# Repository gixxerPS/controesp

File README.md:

# controesp
controllino like board for esp

## PCB size

- base
86.5 x 84 mm
- hat
57 x 80 mm

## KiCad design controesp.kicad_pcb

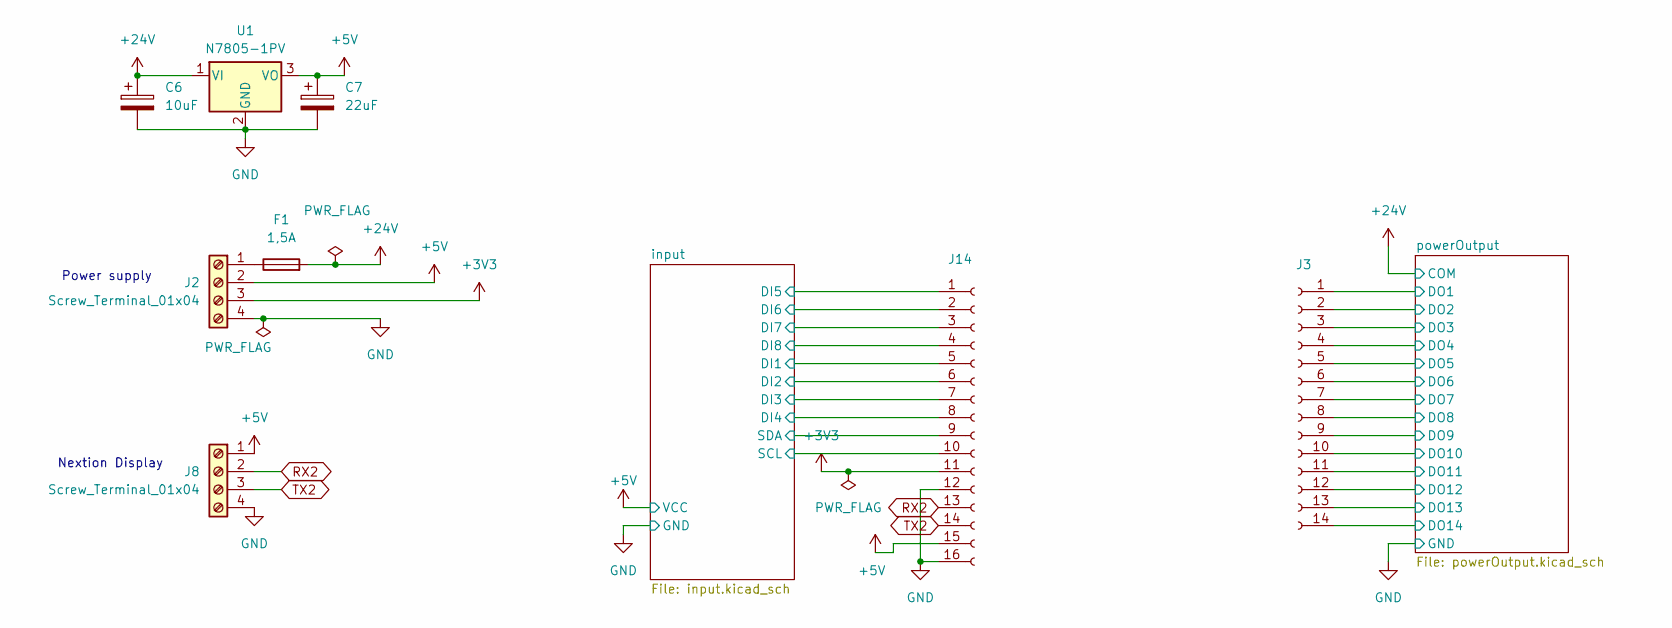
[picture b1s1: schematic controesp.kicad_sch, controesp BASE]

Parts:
C6: 10uF; CP_EIA-3216-12_Kemet-S_Pad1.58x1.35mm_HandSolder; LCSC C13585
C7: 22uF; CP_EIA-2012-12_Kemet-R_Pad1.30x1.05mm_HandSolder; LCSC C45783
F1: 1,5A; Fuseholder_Littelfuse_Nano2_154x
J2, J8: Screw_Terminal_01x04; PhoenixContact_MC_1,5_4-G-3.5_1x04_P3.50mm_Horizontal; LCSC C5241865
J3: Conn_01x14_Socket; PinSocket_1x14_P2.54mm_Vertical; LCSC C52711
J14: Conn_01x16_Socket; PinSocket_1x16_P2.54mm_Vertical; LCSC C66987
U1: N7805-1PV; TO-220-3_Vertical

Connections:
+3V3: J2.3, J14.11
+5V: C7.1, J2.2, J8.1, J14.15, U1.3 (VO); also elsewhere on the board
+24V: C6.1, F1.2, U1.1 (VI); also elsewhere on the board
/input/DI1: J14.5; also elsewhere on the board
/input/DI2: J14.6; also elsewhere on the board
/input/DI3: J14.7; also elsewhere on the board
/input/DI4: J14.8; also elsewhere on the board
/input/DI5: J14.1; also elsewhere on the board
/input/DI6: J14.2; also elsewhere on the board
/input/DI7: J14.3; also elsewhere on the board
/input/DI8: J14.4; also elsewhere on the board
/input/SCL: J14.10; also elsewhere on the board
/input/SDA: J14.9; also elsewhere on the board
/powerOutput/DO1: J3.1; also elsewhere on the board
/powerOutput/DO2: J3.2; also elsewhere on the board
/powerOutput/DO3: J3.3; also elsewhere on the board
/powerOutput/DO4: J3.4; also elsewhere on the board
/powerOutput/DO5: J3.5; also elsewhere on the board
/powerOutput/DO6: J3.6; also elsewhere on the board
/powerOutput/DO7: J3.7; also elsewhere on the board
/powerOutput/DO8: J3.8; also elsewhere on the board
/powerOutput/DO9: J3.9; also elsewhere on the board
/powerOutput/DO10: J3.10; also elsewhere on the board
/powerOutput/DO11: J3.11; also elsewhere on the board
/powerOutput/DO12: J3.12; also elsewhere on the board
/powerOutput/DO13: J3.13; also elsewhere on the board
/powerOutput/DO14: J3.14; also elsewhere on the board
GND: C6.2, C7.2, J2.4, J8.4, J14.12, J14.16, U1.2 (GND); also elsewhere on the board
unnamed: F1.1, J2.1
RX2: J8.2, J14.13
TX2: J8.3, J14.14

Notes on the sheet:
Power supply
Nextion Display

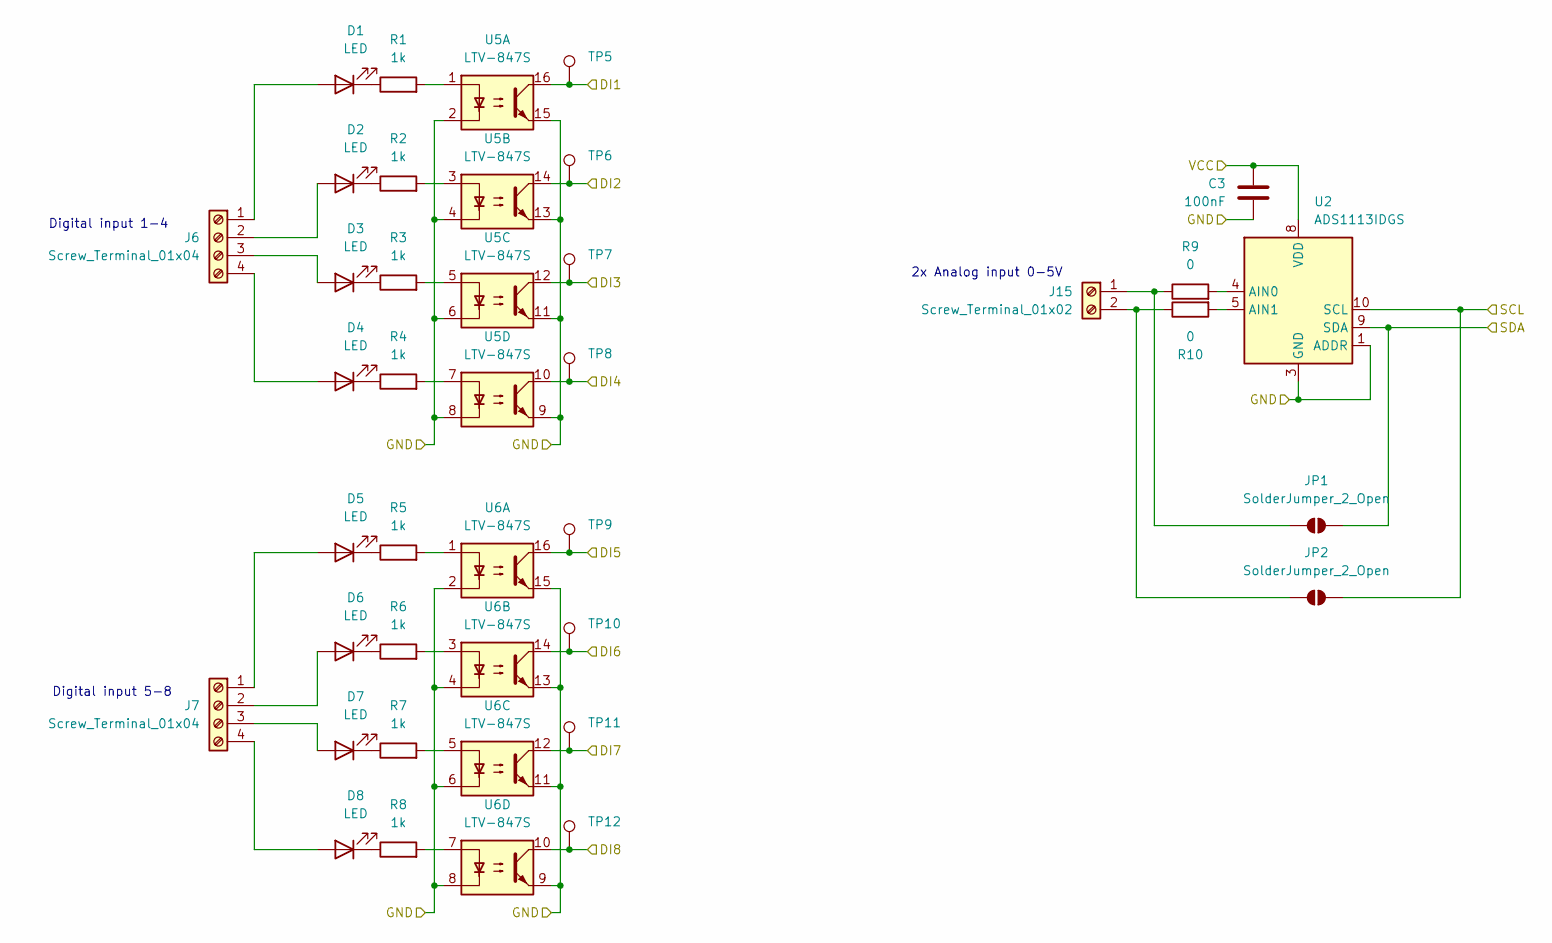
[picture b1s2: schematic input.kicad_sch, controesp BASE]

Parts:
C3: 100nF; C_0805_2012Metric_Pad1.18x1.45mm_HandSolder; LCSC C49678
D1, D2, D3, D4, D5, D6, D7, D8: LED; LED_0805_2012Metric_Pad1.15x1.40mm_HandSolder; LCSC C2297
J6, J7: Screw_Terminal_01x04; PhoenixContact_MC_1,5_4-G-3.5_1x04_P3.50mm_Horizontal; LCSC C5241865
J15: Screw_Terminal_01x02; PhoenixContact_MC_1,5_2-G-3.5_1x02_P3.50mm_Horizontal; LCSC C61791
JP1, JP2: SolderJumper_2_Open; SolderJumper-2_P1.3mm_Open_Pad1.0x1.5mm
R1, R2, R3, R4, R5, R6, R7, R8: 1k; R_0805_2012Metric_Pad1.20x1.40mm_HandSolder; LCSC C17513
R9, R10: 0; R_0805_2012Metric_Pad1.20x1.40mm_HandSolder; LCSC C17477
TP5, TP6, TP7, TP8, TP9, TP10, TP11, TP12: TestPoint_Pad_D1.5mm
U2: ADS1113IDGS; TSSOP-10_3x3mm_P0.5mm; LCSC C2651336
U5: LTV-847S; SMDIP-16_W9.53mm; LCSC C114599
U6: LTV-847S; SMDIP-16_W9.53mm

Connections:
+5V: C3.1, U2.8 (VDD); also elsewhere on the board
/input/DI1: TP5.1, U5.16; also elsewhere on the board
/input/DI2: TP6.1, U5.14; also elsewhere on the board
/input/DI3: TP7.1, U5.12; also elsewhere on the board
/input/DI4: TP8.1, U5.10; also elsewhere on the board
/input/DI5: TP9.1, U6.16; also elsewhere on the board
/input/DI6: TP10.1, U6.14; also elsewhere on the board
/input/DI7: TP11.1, U6.12; also elsewhere on the board
/input/DI8: TP12.1, U6.10; also elsewhere on the board
/input/SCL: JP2.2 (B), U2.10 (SCL); also elsewhere on the board
/input/SDA: JP1.2 (B), U2.9 (SDA); also elsewhere on the board
GND: C3.2, U2.1 (ADDR), U2.3 (GND), U5.2, U5.4, U5.6, U5.8, U5.9, U5.11, U5.13, U5.15, U6.2, U6.4, U6.6, U6.8, U6.9, U6.11, U6.13, U6.15; also elsewhere on the board
unnamed: D1.2 (A), J6.1
unnamed: D1.1 (K), R1.1
unnamed: D2.2 (A), J6.2
unnamed: D2.1 (K), R2.1
unnamed: D3.2 (A), J6.3
unnamed: D3.1 (K), R3.1
unnamed: D4.2 (A), J6.4
unnamed: D4.1 (K), R4.1
unnamed: D5.2 (A), J7.1
unnamed: D5.1 (K), R5.1
unnamed: D6.2 (A), J7.2
unnamed: D6.1 (K), R6.1
unnamed: D7.2 (A), J7.3
unnamed: D7.1 (K), R7.1
unnamed: D8.2 (A), J7.4
unnamed: D8.1 (K), R8.1
unnamed: J15.1, JP1.1 (A), R9.1
unnamed: J15.2, JP2.1 (A), R10.1
unnamed: R1.2, U5.1
unnamed: R2.2, U5.3
unnamed: R3.2, U5.5
unnamed: R4.2, U5.7
unnamed: R5.2, U6.1
unnamed: R6.2, U6.3
unnamed: R7.2, U6.5
unnamed: R8.2, U6.7
unnamed: R9.2, U2.4 (AIN0)
unnamed: R10.2, U2.5 (AIN1)

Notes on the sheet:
2x Analog input 0-5V
Digital input 5-8
Digital input 1-4

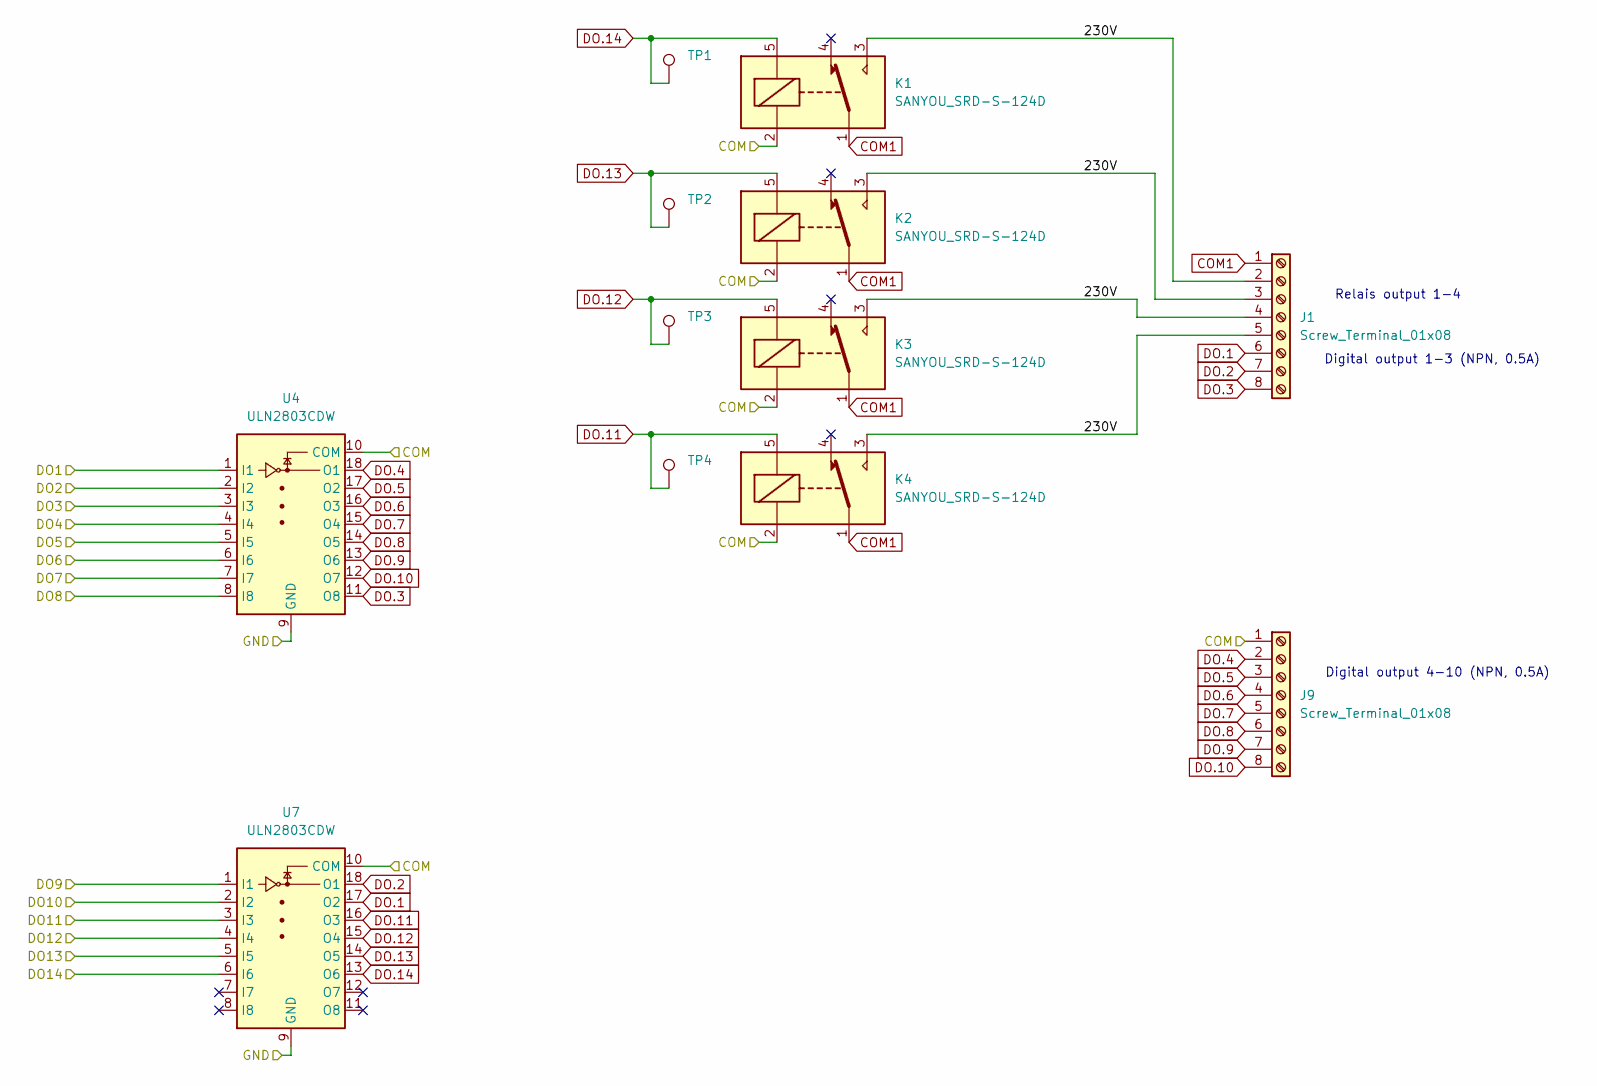
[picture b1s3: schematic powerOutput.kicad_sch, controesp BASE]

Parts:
J1, J9: Screw_Terminal_01x08; TerminalBlock_RND_205-00293_1x08_P5.08mm_Horizontal; LCSC C27587
K1, K2, K3, K4: SANYOU_SRD-S-124D; Relay_SPDT_SANYOU_SRD_Series_Form_C; LCSC C276436
TP1, TP2, TP3, TP4: TestPoint_Pad_D1.5mm
U4, U7: ULN2803CDW; SOIC-20W_7.5x12.8mm_P1.27mm; LCSC C7494313

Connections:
+24V: J9.1, K1.2, K2.2, K3.2, K4.2, U4.10 (COM), U7.10 (COM); also elsewhere on the board
/powerOutput/230V: J1.2, J1.3, J1.4, J1.5, K1.3, K2.3, K3.3, K4.3
/powerOutput/DO1: U4.1 (I1); also elsewhere on the board
/powerOutput/DO2: U4.2 (I2); also elsewhere on the board
/powerOutput/DO3: U4.3 (I3); also elsewhere on the board
/powerOutput/DO4: U4.4 (I4); also elsewhere on the board
/powerOutput/DO5: U4.5 (I5); also elsewhere on the board
/powerOutput/DO6: U4.6 (I6); also elsewhere on the board
/powerOutput/DO7: U4.7 (I7); also elsewhere on the board
/powerOutput/DO8: U4.8 (I8); also elsewhere on the board
/powerOutput/DO9: U7.1 (I1); also elsewhere on the board
/powerOutput/DO10: U7.2 (I2); also elsewhere on the board
/powerOutput/DO11: U7.3 (I3); also elsewhere on the board
/powerOutput/DO12: U7.4 (I4); also elsewhere on the board
/powerOutput/DO13: U7.5 (I5); also elsewhere on the board
/powerOutput/DO14: U7.6 (I6); also elsewhere on the board
COM1: J1.1, K1.1, K2.1, K3.1, K4.1
DO.1: J1.6, U7.17 (O2)
DO.2: J1.7, U7.18 (O1)
DO.3: J1.8, U4.11 (O8)
DO.4: J9.2, U4.18 (O1)
DO.5: J9.3, U4.17 (O2)
DO.6: J9.4, U4.16 (O3)
DO.7: J9.5, U4.15 (O4)
DO.8: J9.6, U4.14 (O5)
DO.9: J9.7, U4.13 (O6)
DO.10: J9.8, U4.12 (O7)
DO.11: K4.5, TP4.1, U7.16 (O3)
DO.12: K3.5, TP3.1, U7.15 (O4)
DO.13: K2.5, TP2.1, U7.14 (O5)
DO.14: K1.5, TP1.1, U7.13 (O6)
GND: U4.9 (GND), U7.9 (GND); also elsewhere on the board

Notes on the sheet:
Digital output 1-3 (NPN, 0.5A)
Relais output 1-4
Digital output 4-10 (NPN, 0.5A)

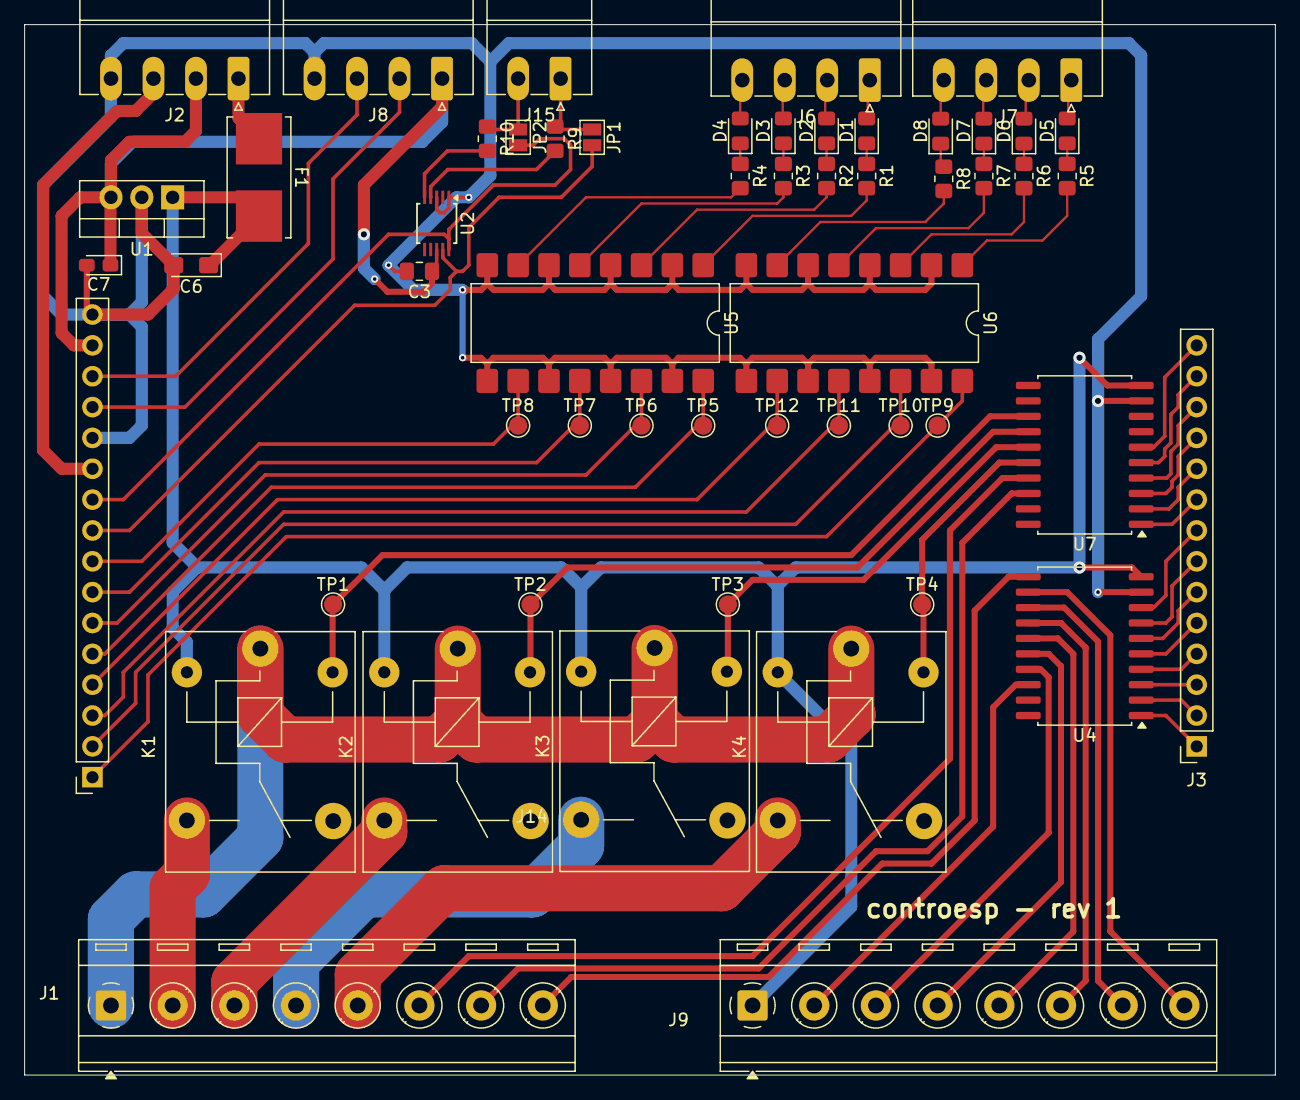
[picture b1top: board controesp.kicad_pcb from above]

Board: 2 copper layers, 103.0 x 86.5 mm, 55 parts (0 on the bottom side), 75 nets.

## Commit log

2025-03-17 added pcb dimensions in README
2025-03-19 merged seperate projects
2025-03-20 added part numbers
2025-03-21 small progress on pcb
2025-03-21 larger pcb
2025-03-23 added fuse and c for 7805
2025-03-26 hat routing finished
2025-03-27 started base layout
2025-03-30 von ben
2025-04-03 pcb layout finished
2025-04-21 almost done
2025-04-21 splitted hat pcb into seperate proj
2025-06-12 added artifacts
